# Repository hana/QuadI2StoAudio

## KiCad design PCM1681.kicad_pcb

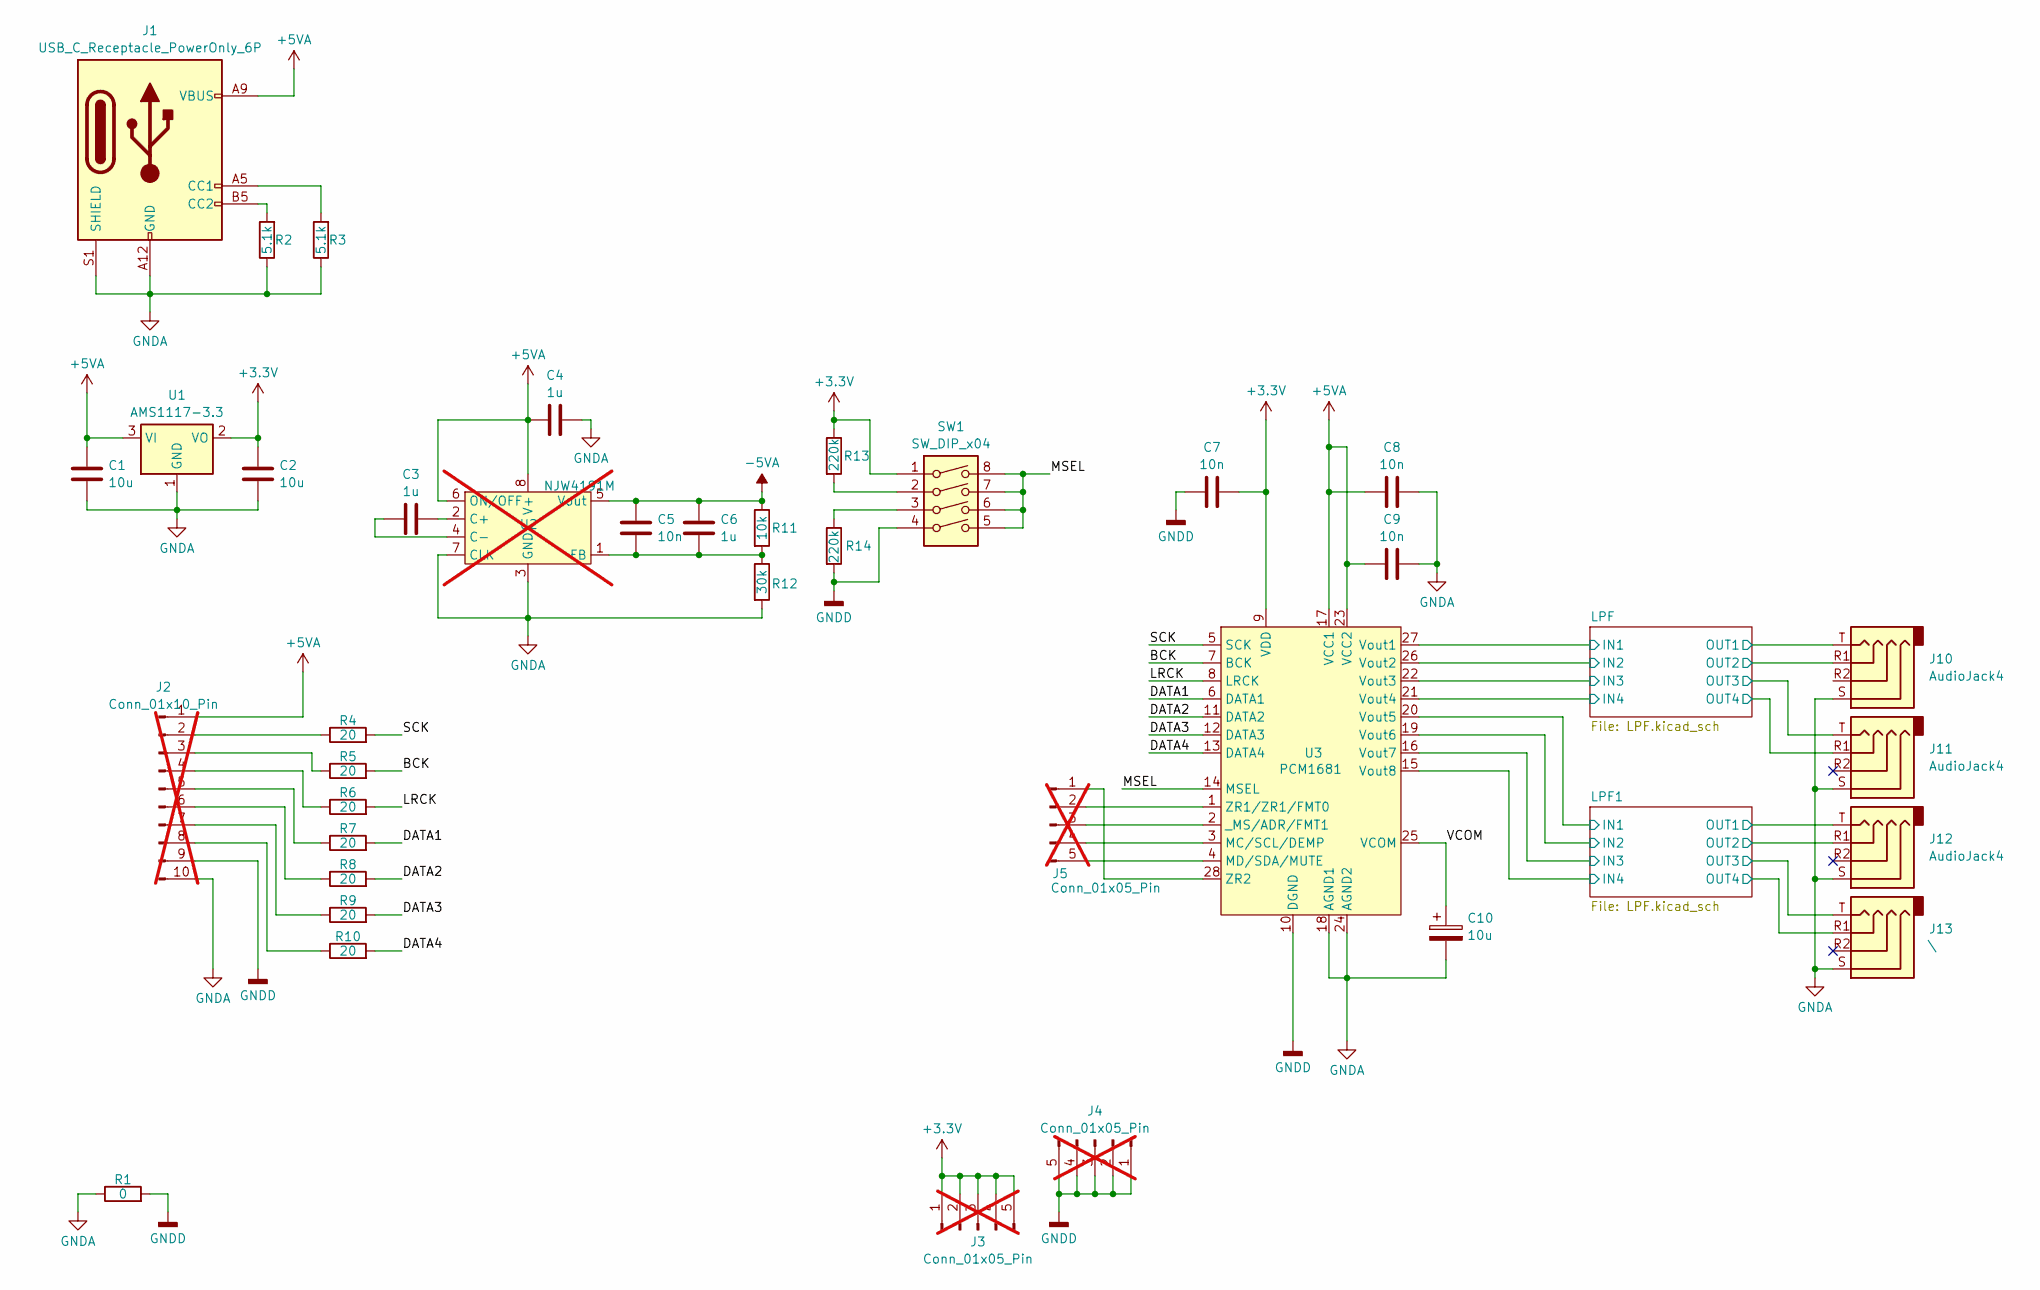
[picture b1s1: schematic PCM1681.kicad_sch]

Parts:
C1, C2, C10: 10u; C_0402_1005Metric; LCSC C15525
C3, C4, C6: 1u; C_0402_1005Metric; LCSC C52923
C5, C7, C8, C9: 10n; C_0402_1005Metric; LCSC C15195
J1: USB_C_Receptacle_PowerOnly_6P; USB_C_Receptacle_GCT_USB4125-xx-x_6P_TopMnt_Horizontal; LCSC C668623
J2: Conn_01x10_Pin; PinHeader_1x10_P2.54mm_Vertical; not fitted
J3, J4, J5: Conn_01x05_Pin; PinHeader_1x05_P2.54mm_Vertical; not fitted
J10, J11, J12: AudioJack4; Jack_3.5mm_PJ320D_Horizontal; LCSC C95562
J13: \; Jack_3.5mm_PJ320D_Horizontal; LCSC C95562
R1: 0; R_0402_1005Metric; LCSC C17168
R2, R3: 5.1k; R_0402_1005Metric; LCSC C25905
R4, R5, R6, R7, R8, R9, R10: 20; R_0603_1608Metric; LCSC C22950
R11: 10k; R_0402_1005Metric; LCSC C25744
R12: 30k; R_0603_1608Metric; LCSC C22984
R13, R14: 220k; R_0603_1608Metric; LCSC C22961
SW1: SW_DIP_x04; SW_DIP_SPSTx04_Slide_KingTek_DSHP04TJ_W5.25mm_P1.27mm_JPin; LCSC C224996
U1: AMS1117-3.3; SOT-223-3_TabPin2; LCSC C6186
U2: NJW4191M; SOIC-8_5.3x5.3mm_P1.27mm; not fitted
U3: PCM1681; HTSSOP-28-1EP_4.4x9.7mm_P0.65mm_EP2.75x6.2mm; LCSC C181571

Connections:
+3.3V: C2.2, C7.2, J3.1, J3.2, J3.3, J3.4, J3.5, R13.1, SW1.1, U1.2 (VO), U3.9 (VDD)
+5VA: C1.2, C4.1, C8.1, C9.1, J1.A9 (VBUS), J1.B9 (VBUS), J2.1, U1.3 (VI), U2.6 (ON/OFF), U2.8 (V+), U3.17 (VCC1), U3.23 (VCC2); also elsewhere on the board
-5VA: C5.2, C6.2, R11.1, U2.5 (Vout); also elsewhere on the board
/BCK: R5.2, U3.7 (BCK)
/DATA1: R7.2, U3.6 (DATA1)
/DATA2: R8.2, U3.11 (DATA2)
/DATA3: R9.2, U3.12 (DATA3)
/DATA4: R10.2, U3.13 (DATA4)
/LPF1/IN1: U3.20 (Vout5); also elsewhere on the board
/LPF1/IN2: U3.19 (Vout6); also elsewhere on the board
/LPF1/IN3: U3.16 (Vout7); also elsewhere on the board
/LPF1/IN4: U3.15 (Vout8); also elsewhere on the board
/LPF1/OUT1: J12.T; also elsewhere on the board
/LPF1/OUT2: J12.R1; also elsewhere on the board
/LPF1/OUT3: J13.T; also elsewhere on the board
/LPF1/OUT4: J13.R1; also elsewhere on the board
/LPF/IN1: U3.27 (Vout1); also elsewhere on the board
/LPF/IN2: U3.26 (Vout2); also elsewhere on the board
/LPF/IN3: U3.22 (Vout3); also elsewhere on the board
/LPF/IN4: U3.21 (Vout4); also elsewhere on the board
/LPF/OUT1: J10.T; also elsewhere on the board
/LPF/OUT2: J10.R1; also elsewhere on the board
/LPF/OUT3: J11.T; also elsewhere on the board
/LPF/OUT4: J11.R1; also elsewhere on the board
/LRCK: R6.2, U3.8 (LRCK)
/MSEL: SW1.5, SW1.6, SW1.7, SW1.8, U3.14 (MSEL)
/SCK: R4.2, U3.5 (SCK)
/VCOM: C10.1, U3.25 (VCOM)
GNDA: C1.1, C2.1, C4.2, C8.2, C9.2, C10.2, J1.A12 (GND), J1.B12 (GND), J1.S1 (SHIELD), J2.10, J10.S, J11.S, J12.S, J13.S, R1.1, R2.1, R3.1, R12.2, U1.1 (GND), U2.3 (GND), U2.7 (CLK), U3.18 (AGND1), U3.24 (AGND2); also elsewhere on the board
GNDD: C7.1, J2.9, J4.1, J4.2, J4.3, J4.4, J4.5, R1.2, R14.2, SW1.4, U3.10 (DGND)
unnamed: J1.A5 (CC1), R3.2
unnamed: J1.B5 (CC2), R2.2
unnamed: J2.2, R4.1
unnamed: J2.3, R5.1
unnamed: J2.4, R6.1
unnamed: J2.5, R7.1
unnamed: J2.6, R8.1
unnamed: J2.7, R9.1
unnamed: J2.8, R10.1
unnamed: J5.1, U3.28 (ZR2)
unnamed: J5.2, U3.1 (ZR1/ZR1/FMT0)
unnamed: J5.3, U3.2 (_MS/ADR/FMT1)
unnamed: J5.4, U3.3 (MC/SCL/DEMP)
unnamed: J5.5, U3.4 (MD/SDA/MUTE)
unnamed: R13.2, SW1.2
unnamed: R14.1, SW1.3
unnamed: C3.2, U2.2 (C+)
unnamed: C3.1, U2.4 (C-)
unnamed: C5.1, C6.1, R11.2, R12.1, U2.1 (FB)

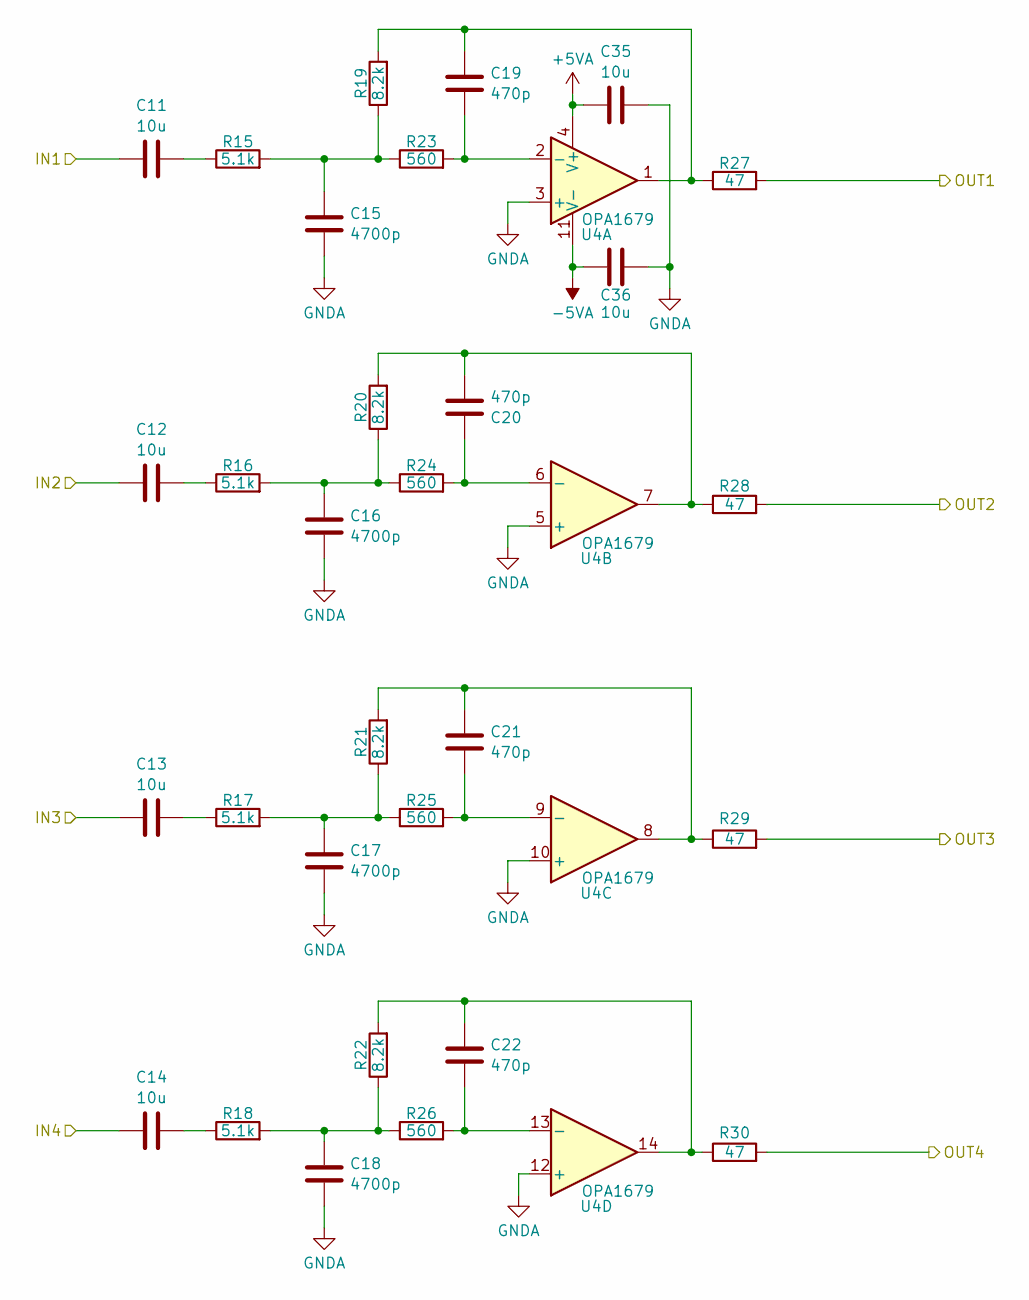
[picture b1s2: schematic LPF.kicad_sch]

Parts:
C11, C12, C13, C14, C35, C36: 10u; C_0402_1005Metric; LCSC C15525
C15, C16, C17, C18: 4700p; C_0402_1005Metric; LCSC C1538
C19, C20, C21, C22: 470p; C_0603_1608Metric; LCSC C1620
R15, R16, R17, R18: 5.1k; R_0402_1005Metric; LCSC C25905
R19, R20, R21, R22: 8.2k; R_0603_1608Metric; LCSC C25981
R23, R24, R25, R26: 560; R_0603_1608Metric; LCSC C23204
R27, R28, R29, R30: 47; R_0603_1608Metric; LCSC C23182
U4: OPA1679; QFN-16-1EP_4x4mm_P0.65mm_EP2.1x2.1mm; LCSC C1849432

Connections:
+5VA: C35.1, U4.4 (V+); also elsewhere on the board
-5VA: C36.1, U4.11 (V-); also elsewhere on the board
/LPF/IN1: C11.1; also elsewhere on the board
/LPF/IN2: C12.1; also elsewhere on the board
/LPF/IN3: C13.1; also elsewhere on the board
/LPF/IN4: C14.1; also elsewhere on the board
/LPF/OUT1: R27.2; also elsewhere on the board
/LPF/OUT2: R28.2; also elsewhere on the board
/LPF/OUT3: R29.2; also elsewhere on the board
/LPF/OUT4: R30.2; also elsewhere on the board
GNDA: C15.2, C16.2, C17.2, C18.2, C35.2, C36.2, U4.3 (+), U4.5 (+), U4.10 (+), U4.12 (+); also elsewhere on the board
unnamed: C11.2, R15.1
unnamed: C12.2, R16.1
unnamed: C13.2, R17.1
unnamed: C14.2, R18.1
unnamed: C15.1, R15.2, R19.1, R23.1
unnamed: C16.1, R16.2, R20.1, R24.1
unnamed: C17.1, R17.2, R21.1, R25.1
unnamed: C18.1, R18.2, R22.1, R26.1
unnamed: C19.1, R19.2, R27.1, U4.1
unnamed: C20.2, R20.2, R28.1, U4.7
unnamed: C21.1, R21.2, R29.1, U4.8
unnamed: C22.1, R22.2, R30.1, U4.14
unnamed: C19.2, R23.2, U4.2 (-)
unnamed: C20.1, R24.2, U4.6 (-)
unnamed: C21.2, R25.2, U4.9 (-)
unnamed: C22.2, R26.2, U4.13 (-)

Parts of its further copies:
C23, C24, C25, C26, C37, C38: 10u; C_0402_1005Metric; LCSC C15525
C27, C28, C29, C30: 4700p; C_0402_1005Metric; LCSC C1538
C31, C32, C33, C34: 470p; C_0603_1608Metric; LCSC C1620
R31, R32, R33, R34: 5.1k; R_0402_1005Metric; LCSC C25905
R35, R36, R37, R38: 8.2k; R_0603_1608Metric; LCSC C25981
R39, R40, R41, R42: 560; R_0603_1608Metric; LCSC C23204
R43, R44, R45, R46: 47; R_0603_1608Metric; LCSC C23182
U5: OPA1679; QFN-16-1EP_4x4mm_P0.65mm_EP2.1x2.1mm; LCSC C1849432

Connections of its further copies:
+5VA: C37.1, U5.4 (V+); also elsewhere on the board
-5VA: C38.1, U5.11 (V-); also elsewhere on the board
/LPF1/IN1: C23.1; also elsewhere on the board
/LPF1/IN2: C24.1; also elsewhere on the board
/LPF1/IN3: C25.1; also elsewhere on the board
/LPF1/IN4: C26.1; also elsewhere on the board
/LPF1/OUT1: R43.2; also elsewhere on the board
/LPF1/OUT2: R44.2; also elsewhere on the board
/LPF1/OUT3: R45.2; also elsewhere on the board
/LPF1/OUT4: R46.2; also elsewhere on the board
GNDA: C27.2, C28.2, C29.2, C30.2, C37.2, C38.2, U5.3 (+), U5.5 (+), U5.10 (+), U5.12 (+); also elsewhere on the board
unnamed: C23.2, R31.1
unnamed: C24.2, R32.1
unnamed: C25.2, R33.1
unnamed: C26.2, R34.1
unnamed: C27.1, R31.2, R35.1, R39.1
unnamed: C28.1, R32.2, R36.1, R40.1
unnamed: C29.1, R33.2, R37.1, R41.1
unnamed: C30.1, R34.2, R38.1, R42.1
unnamed: C31.1, R35.2, R43.1, U5.1
unnamed: C32.2, R36.2, R44.1, U5.7
unnamed: C33.1, R37.2, R45.1, U5.8
unnamed: C34.1, R38.2, R46.1, U5.14
unnamed: C31.2, R39.2, U5.2 (-)
unnamed: C32.1, R40.2, U5.6 (-)
unnamed: C33.2, R41.2, U5.9 (-)
unnamed: C34.2, R42.2, U5.13 (-)

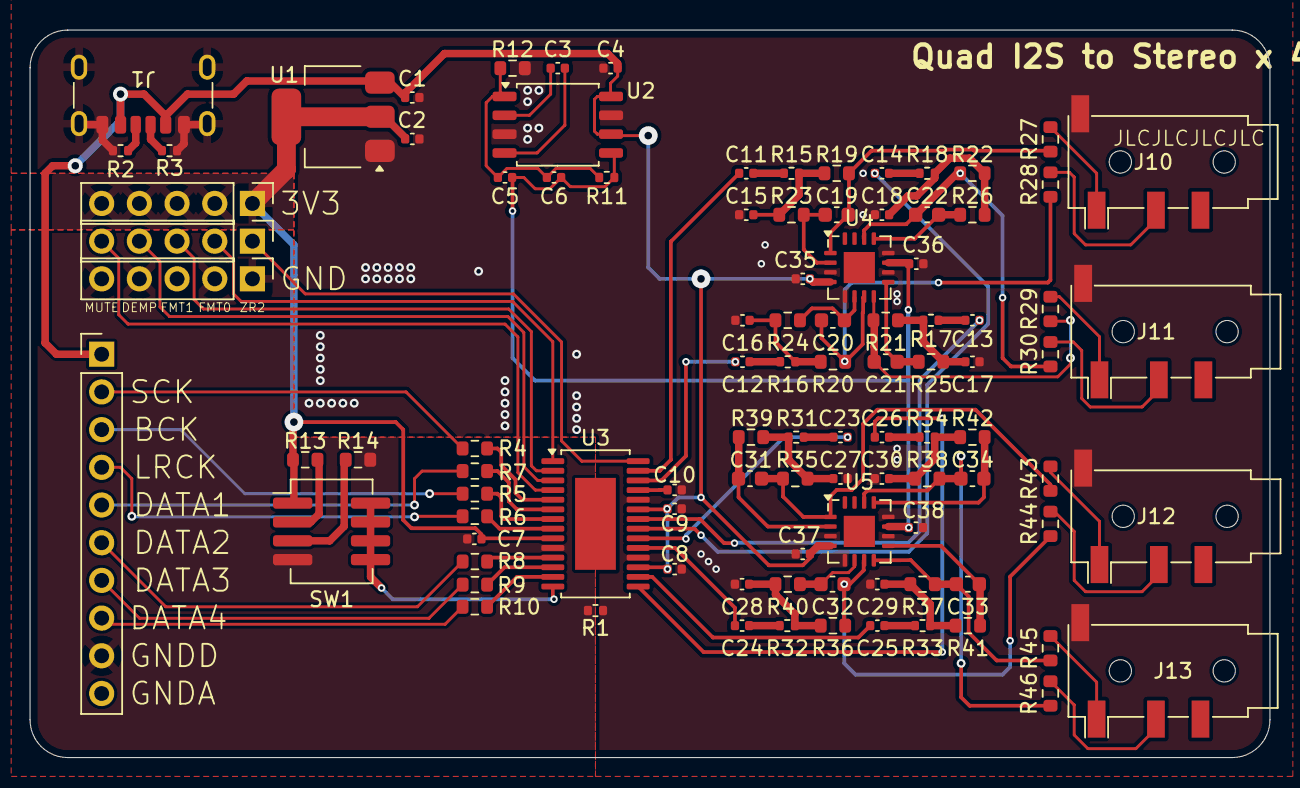
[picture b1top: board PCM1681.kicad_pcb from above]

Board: 2 copper layers, 83.5 x 49.0 mm, 99 parts (0 on the bottom side), 81 nets.

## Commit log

2025-05-13 First order
2025-05-17 Updated LCSC parts number for unmatched footprint
